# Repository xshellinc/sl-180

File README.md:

# SL-180

# Software Installation

## Raspberry Pi

Make sure to use Raspbian.

### Install Node.js

```
curl -sL https://deb.nodesource.com/setup_7.x | sudo -E bash -
sudo apt-get install -y nodejs
```

### Set up i2c

Uncomment line:46 in `/boot/config.txt`.
```
dtparam=i2c_arm=on
```

Add following lines to `/etc/modules`
```
i2c-bcm2708
i2c-dev
```

reboot OS.
```
reboot
```

### Set up Bluetooth

You may need to stop bluetoothd for prevent interference.
```
sudo systemctl stop bluetooth
sudo systemctl disable bluetooth
```

Install bluetooth libraries.
```
sudo apt-get install bluetooth bluez libbluetooth-dev libudev-dev
```

To power bluetooth adapter up.
```
sudo hciconfig hci0 up
```

### Installation

Clone sl-180 repository:
```
git clone https://github.com/xshellinc/sl-180.git
```

The repository inclueds source code for Raspberry Pi, iOS and Arduino.
Move to raspberry directory and install dependencies:
```
cd <PATH TO SL-180>/raspberry/
npm install
```

then, you can start the application with:
```
sudo node index.js
```

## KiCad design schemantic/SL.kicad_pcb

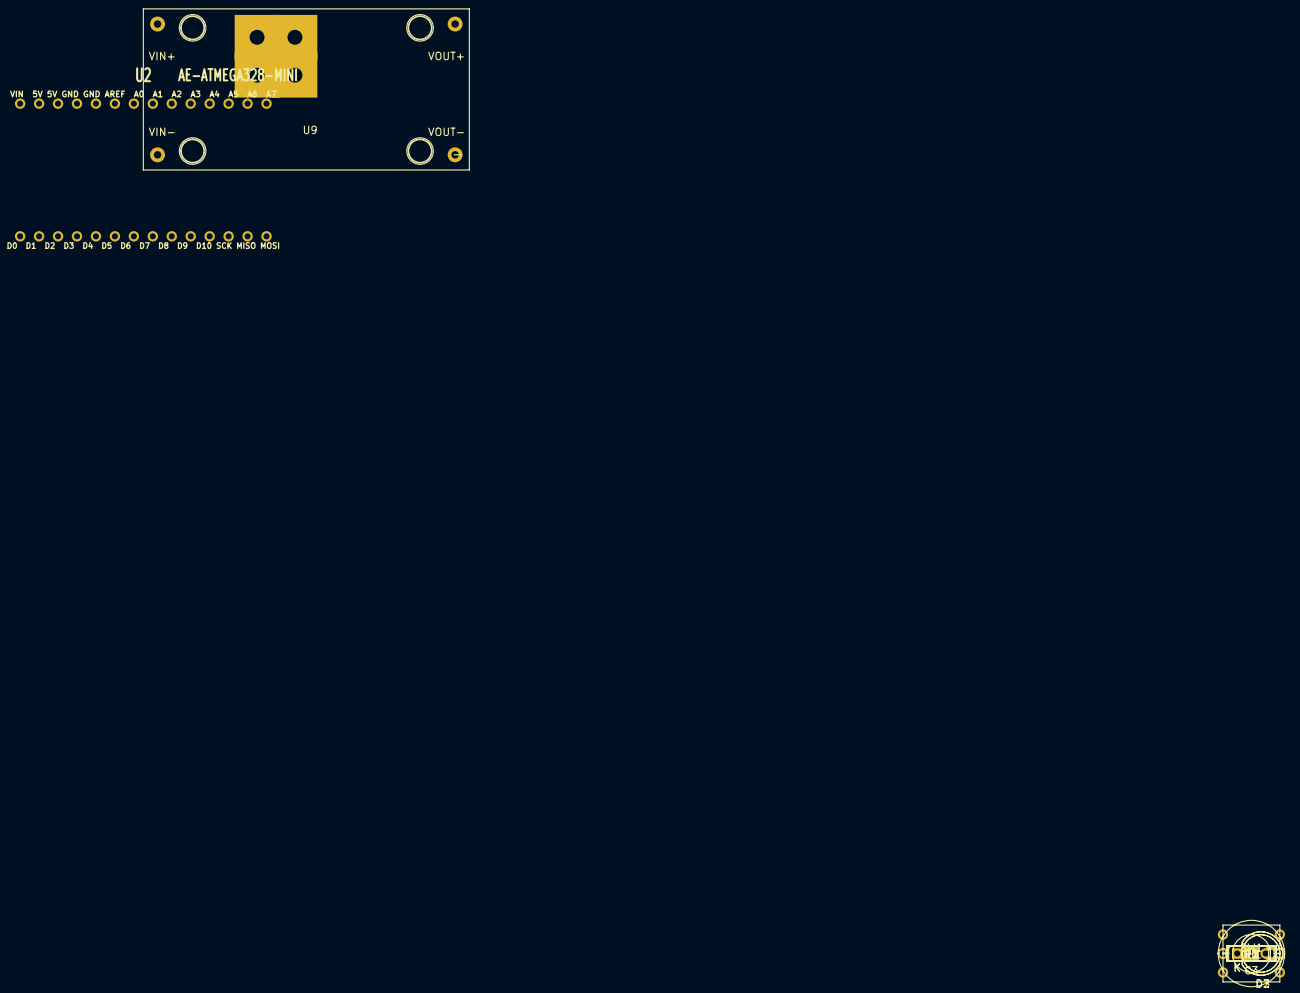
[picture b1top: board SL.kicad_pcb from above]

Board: 2 copper layers, 11 parts (0 on the bottom side), 3 nets, no tracks yet.

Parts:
C3: 100μF; C1.5V8V
D1: D_Schottky; D3
D2, D3: D_Schottky; LED-5MM
R1, R2, R3: 0.156Ω; R3
SW1: RESET; SW_PUSH_SMALL
TH1: THERMISTOR; R3
U2: AE-ATMEGA328-MINI
U9: LM2596HV_DCDC_Module; DCDC_MODULE_LM2596HVS

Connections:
+5V: C3.1, U2.5V
+24V: D1.1, D2.1, D3.1, R1.1, R2.1, R3.1
GND: C3.2, SW1.2, U2.GND

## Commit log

2017-06-28 Add swift project
2017-06-29 Updated BLE device UUID
2017-06-29 Update service id
2017-06-29 Updated sendValue to only send new value
2017-06-30 Add an application for raspi
2017-06-30 Add readme file
2017-06-30 Add bleno to dependencies
2017-06-30 Add systemd unit file and fix typos for readme
2017-07-03 added assets
